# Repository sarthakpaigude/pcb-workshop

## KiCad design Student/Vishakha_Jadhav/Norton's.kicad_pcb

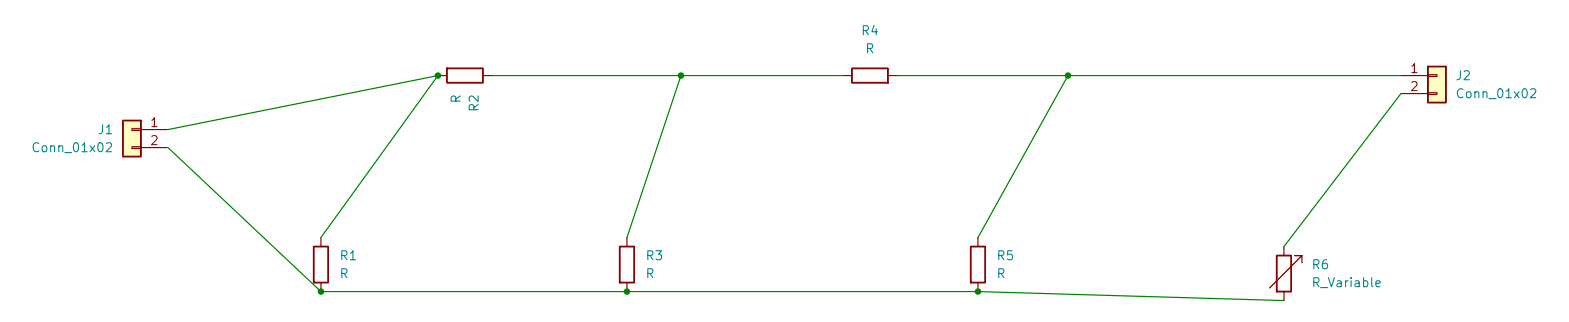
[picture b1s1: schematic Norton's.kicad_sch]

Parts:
J1, J2: Conn_01x02; PinHeader_1x02_P2.54mm_Vertical
R1, R2, R3, R4, R5: R; R_Axial_DIN0207_L6.3mm_D2.5mm_P15.24mm_Horizontal
R6: R_Variable; R_Box_L26.0mm_W5.0mm_P20.00mm

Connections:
unnamed: J1.1, R1.1, R2.2
unnamed: J1.2, R1.2, R3.2, R5.2, R6.2
unnamed: J2.1, R4.2, R5.1
unnamed: J2.2, R6.1
unnamed: R2.1, R3.1, R4.1

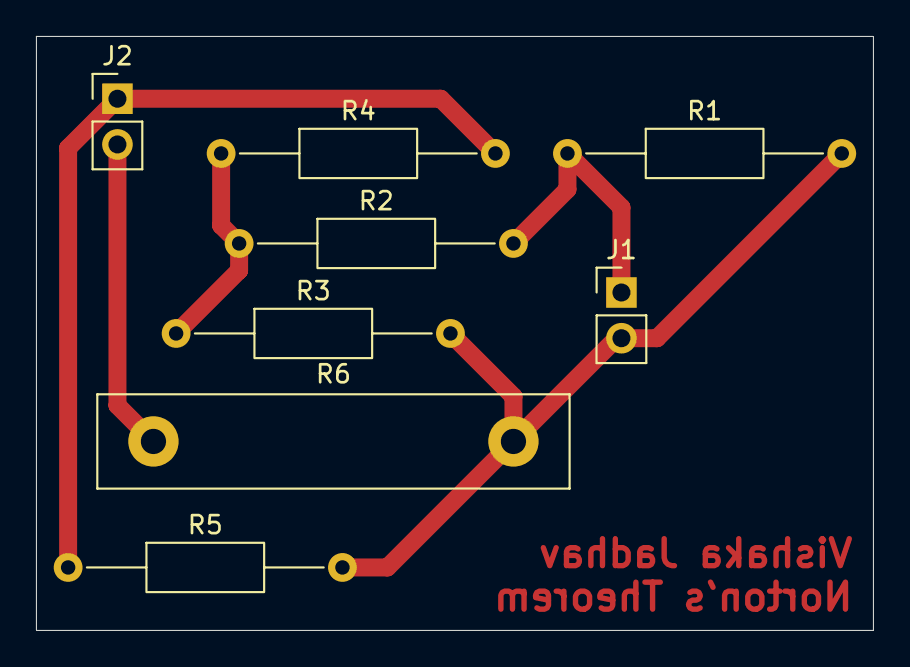
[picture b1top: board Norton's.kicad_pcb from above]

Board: 2 copper layers, 46.5 x 33.0 mm, 8 parts (0 on the bottom side), 5 nets.

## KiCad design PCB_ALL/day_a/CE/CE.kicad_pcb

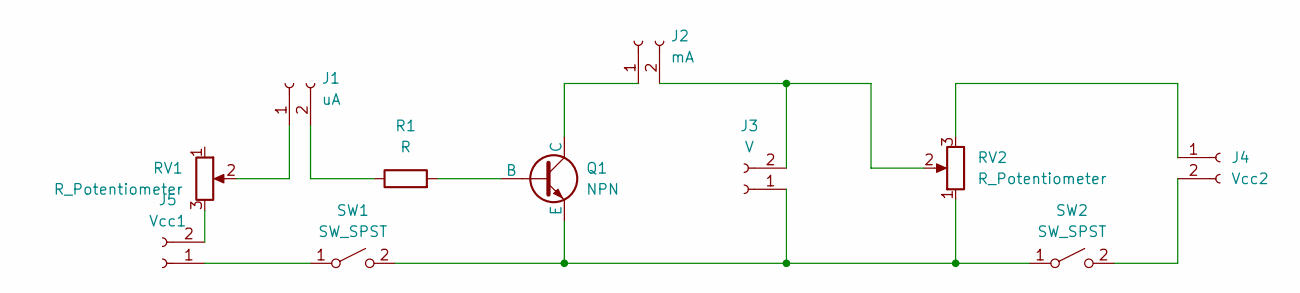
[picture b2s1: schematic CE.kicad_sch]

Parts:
J1: uA; Banana_Jack_2Pin
J2: mA; Banana_Jack_2Pin
J3: V; Banana_Jack_2Pin
J4: Vcc2; Banana_Jack_2Pin
J5: Vcc1; Banana_Jack_2Pin
Q1: NPN; TO-92L_Inline_Wide
R1: R; R_Axial_DIN0204_L3.6mm_D1.6mm_P7.62mm_Horizontal
RV1, RV2: R_Potentiometer; Potentiometer_Vishay_248GJ-249GJ_Single_Vertical
SW1, SW2: SW_SPST; SW_DIP_SPSTx01_Slide_6.7x4.1mm_W7.62mm_P2.54mm_LowProfile

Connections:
unnamed: J1.1, RV1.2
unnamed: J1.2, R1.1
unnamed: J2.1, Q1.1 (C)
unnamed: J2.2, J3.2, RV2.2
unnamed: J3.1, Q1.3 (E), RV2.1, SW1.2 (B), SW2.1 (A)
unnamed: J4.1, RV2.3
unnamed: J4.2, SW2.2 (B)
unnamed: J5.1, SW1.1 (A)
unnamed: J5.2, RV1.3
unnamed: Q1.2 (B), R1.2

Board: 2 copper layers, 11 parts (0 on the bottom side), 10 nets, no tracks yet.

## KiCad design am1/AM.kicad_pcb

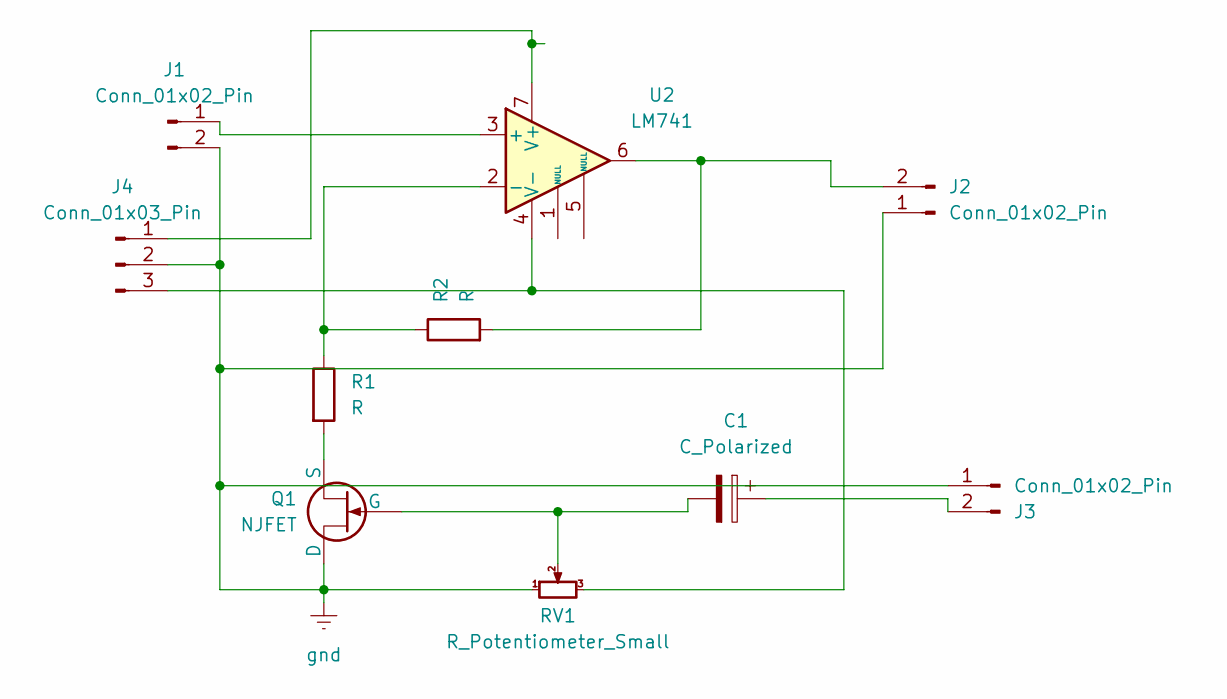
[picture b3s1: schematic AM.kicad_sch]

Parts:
C1: C_Polarized; CP_Radial_D8.0mm_P5.00mm
J1, J2, J3: Conn_01x02_Pin; Banana_Jack_2Pin
J4: Conn_01x03_Pin; Banana_Jack_3Pin
Q1: NJFET; TO-72-4
R1, R2: R; R_Axial_DIN0309_L9.0mm_D3.2mm_P12.70mm_Horizontal
RV1: R_Potentiometer_Small; Potentiometer_Alps_RK163_Single_Horizontal
U2: LM741; DIP-8_W7.62mm

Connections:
unnamed: J1.1, U2.3 (+)
unnamed: J2.2, R2.2, U2.6
unnamed: C1.1, J3.2
unnamed: J4.1, U2.7 (V+)
unnamed: J4.3, RV1.3, U2.4 (V-)
unnamed: C1.2, Q1.2 (G), RV1.2
unnamed: Q1.3 (S), R1.2
unnamed: R1.1, R2.1, U2.2 (-)
gnd: J1.2, J2.1, J3.1, J4.2, Q1.1 (D), RV1.1

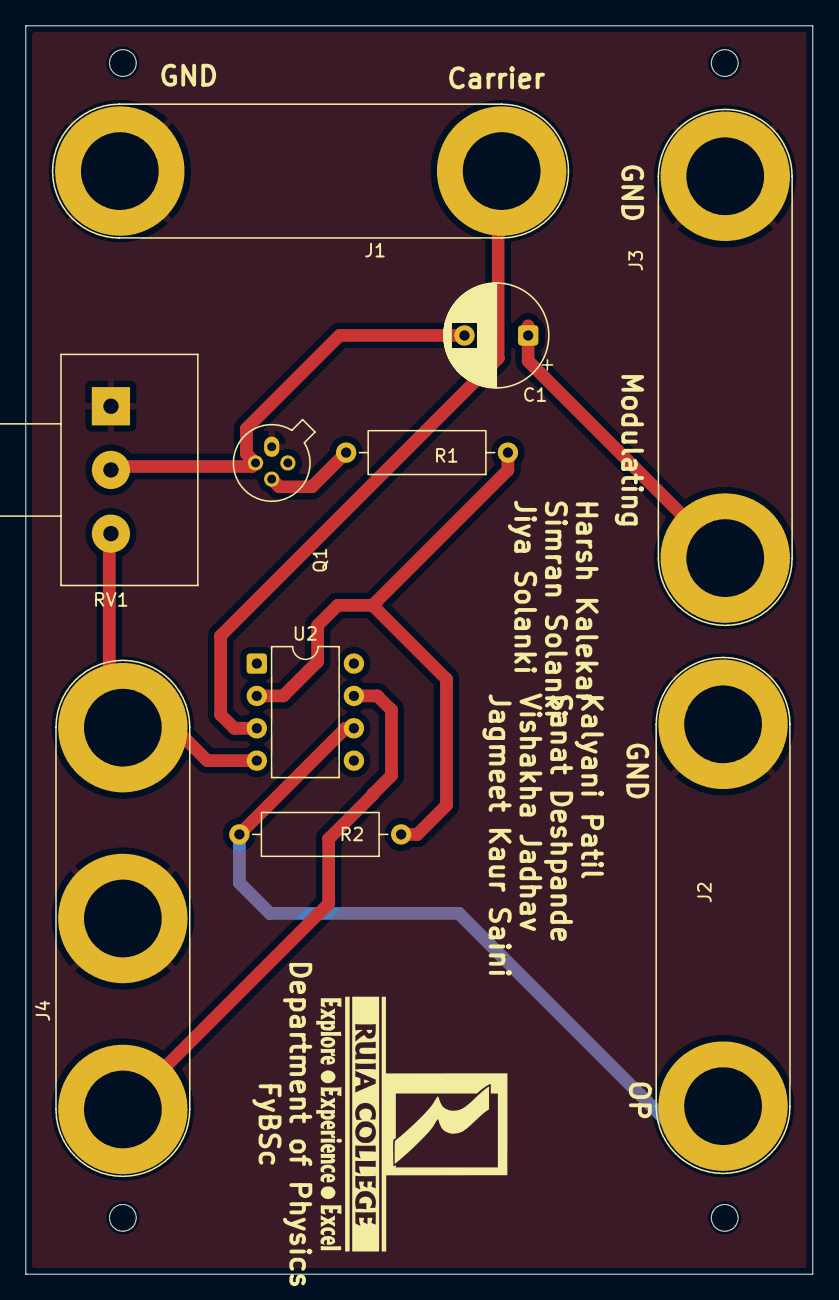
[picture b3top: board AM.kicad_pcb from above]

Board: 2 copper layers, 61.8 x 98.0 mm, 10 parts (0 on the bottom side), 9 nets.

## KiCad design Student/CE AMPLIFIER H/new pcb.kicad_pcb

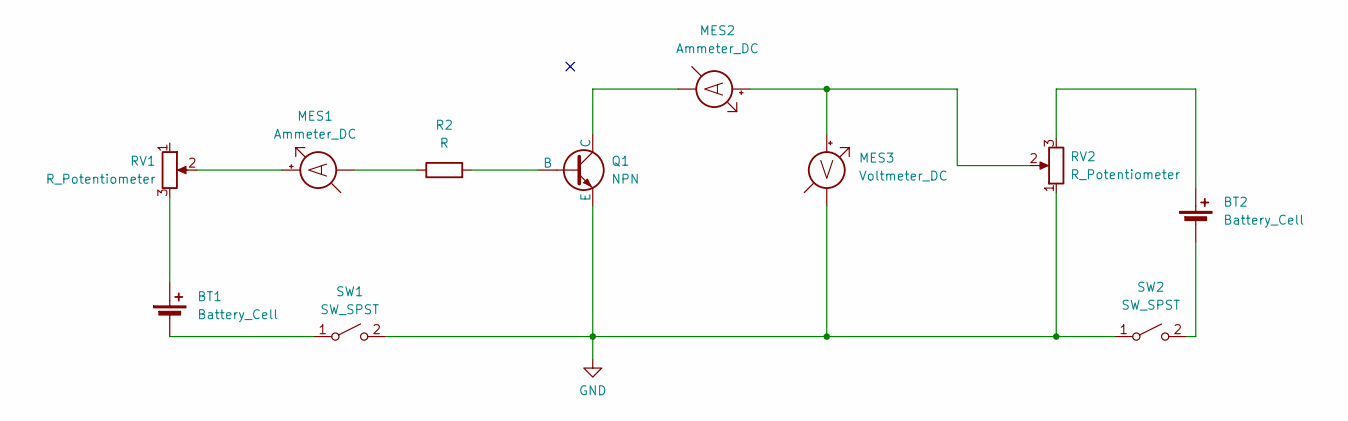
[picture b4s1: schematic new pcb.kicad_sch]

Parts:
BT1, BT2: Battery_Cell; Banana_Jack_2Pin
MES1, MES2: Ammeter_DC; Banana_Jack_2Pin
MES3: Voltmeter_DC; Banana_Jack_2Pin
Q1: NPN; TO-92
R2: R; R_Axial_DIN0207_L6.3mm_D2.5mm_P7.62mm_Horizontal
RV1, RV2: R_Potentiometer; Potentiometer_Vishay_148-149_Single_Vertical
SW1, SW2: SW_SPST; SW_DIP_SPSTx01_Slide_6.7x4.1mm_W7.62mm_P2.54mm_LowProfile

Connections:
GND: MES3.1 (-), Q1.3 (E), RV2.1, SW1.2 (B), SW2.1 (A)
unnamed: BT1.1 (+), RV1.3
unnamed: BT1.2 (-), SW1.1 (A)
unnamed: BT2.1 (+), RV2.3
unnamed: BT2.2 (-), SW2.2 (B)
unnamed: MES1.2 (+), RV1.2
unnamed: MES1.1 (-), R2.1
unnamed: MES2.2 (+), MES3.2 (+), RV2.2
unnamed: MES2.1 (-), Q1.1 (C)
unnamed: Q1.2 (B), R2.2

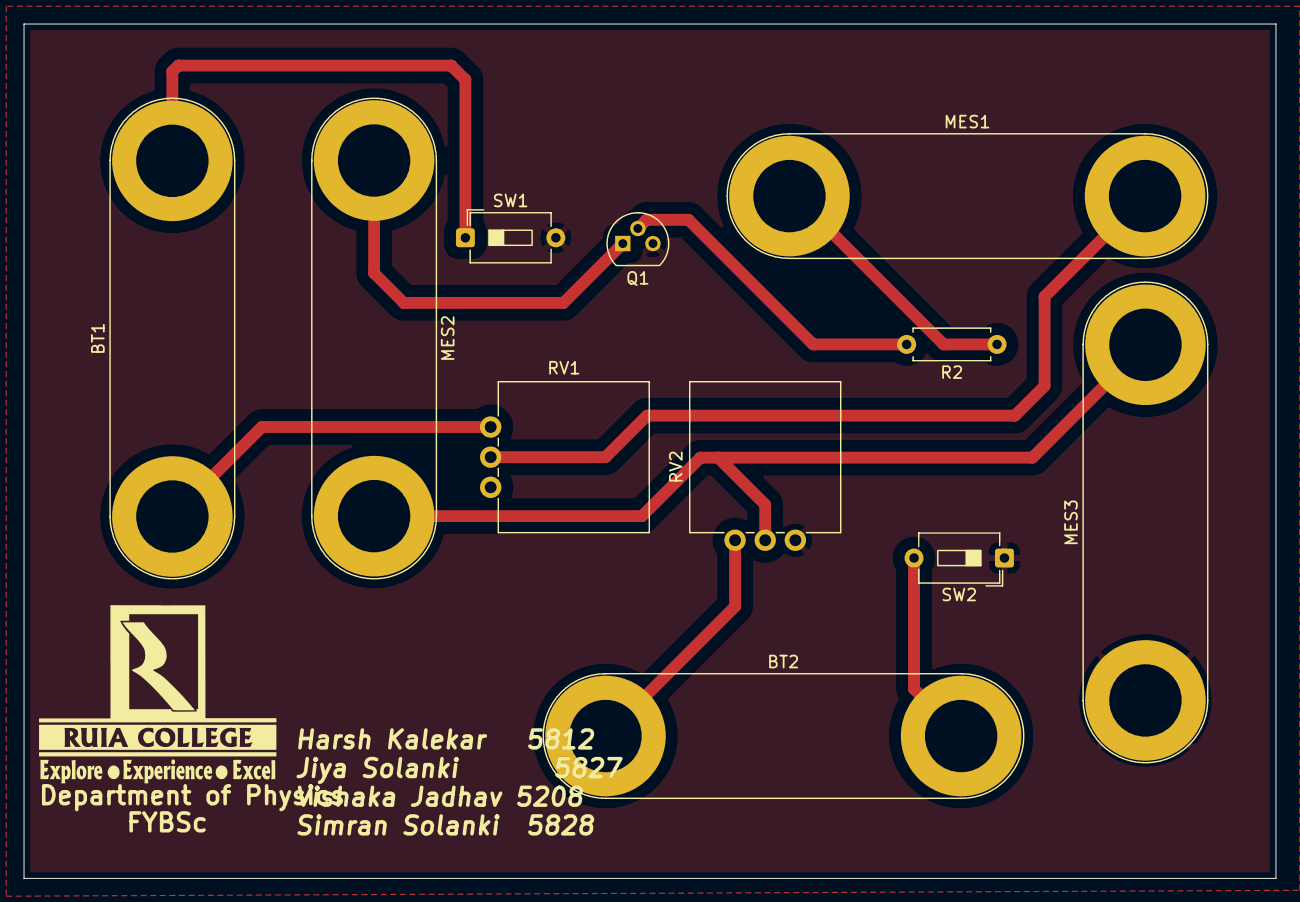
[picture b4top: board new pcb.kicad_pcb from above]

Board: 2 copper layers, 105.5 x 72.0 mm, 11 parts (0 on the bottom side), 10 nets.

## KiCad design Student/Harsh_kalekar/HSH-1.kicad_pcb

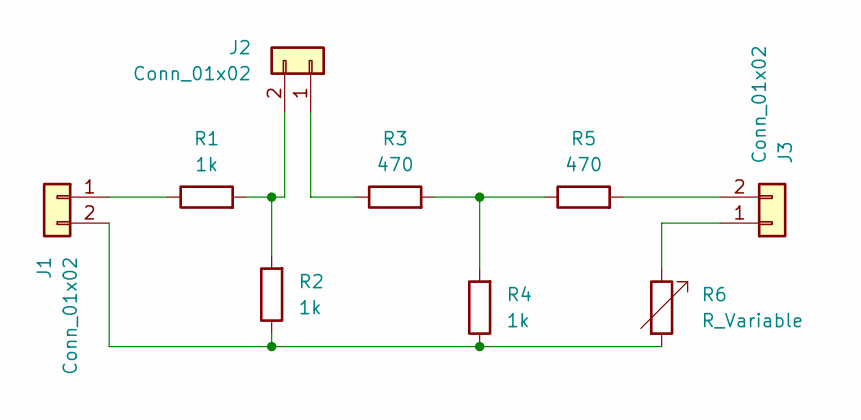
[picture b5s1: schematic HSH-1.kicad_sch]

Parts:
J1, J2, J3: Conn_01x02; PinHeader_1x02_P2.54mm_Vertical
R1, R2, R4: 1k; R_Axial_DIN0207_L6.3mm_D2.5mm_P7.62mm_Horizontal
R3, R5: 470; R_Axial_DIN0207_L6.3mm_D2.5mm_P7.62mm_Horizontal
R6: R_Variable; R_Box_L14.0mm_W5.0mm_P9.00mm

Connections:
unnamed: J1.1, R1.1
unnamed: J1.2, R2.1, R4.1, R6.2
unnamed: J2.1, R3.1
unnamed: J2.2, R1.2, R2.2
unnamed: J3.1, R6.1
unnamed: J3.2, R5.2
unnamed: R3.2, R4.2, R5.1

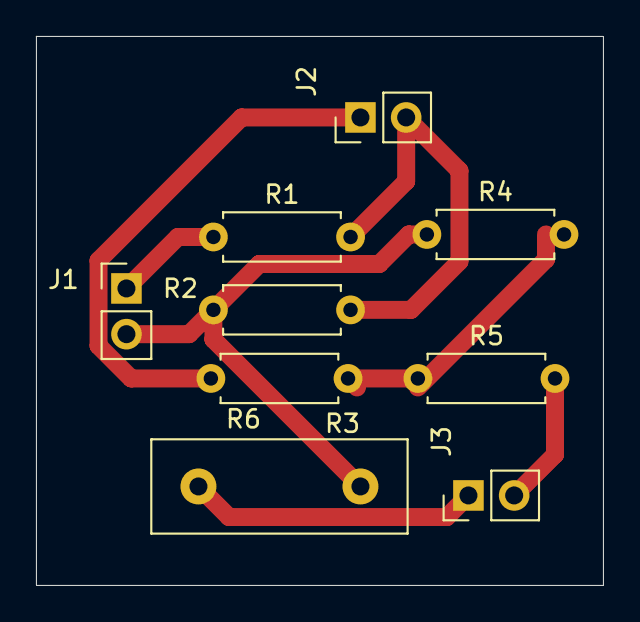
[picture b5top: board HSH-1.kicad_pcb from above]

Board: 2 copper layers, 31.5 x 30.5 mm, 9 parts (0 on the bottom side), 7 nets.

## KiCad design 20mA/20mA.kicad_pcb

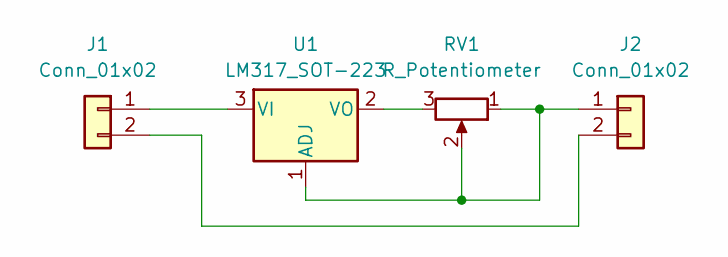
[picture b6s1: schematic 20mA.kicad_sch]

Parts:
J1, J2: Conn_01x02; Banana_Jack_2Pin
RV1: R_Potentiometer; Potentiometer_Runtron_RM-063_Horizontal
U1: LM317_SOT-223; SOT-223-3_TabPin2

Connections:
unnamed: J1.1, U1.3 (VI)
unnamed: J1.2, J2.2
unnamed: J2.1, RV1.1, RV1.2, U1.1 (ADJ)
unnamed: RV1.3, U1.2 (VO)

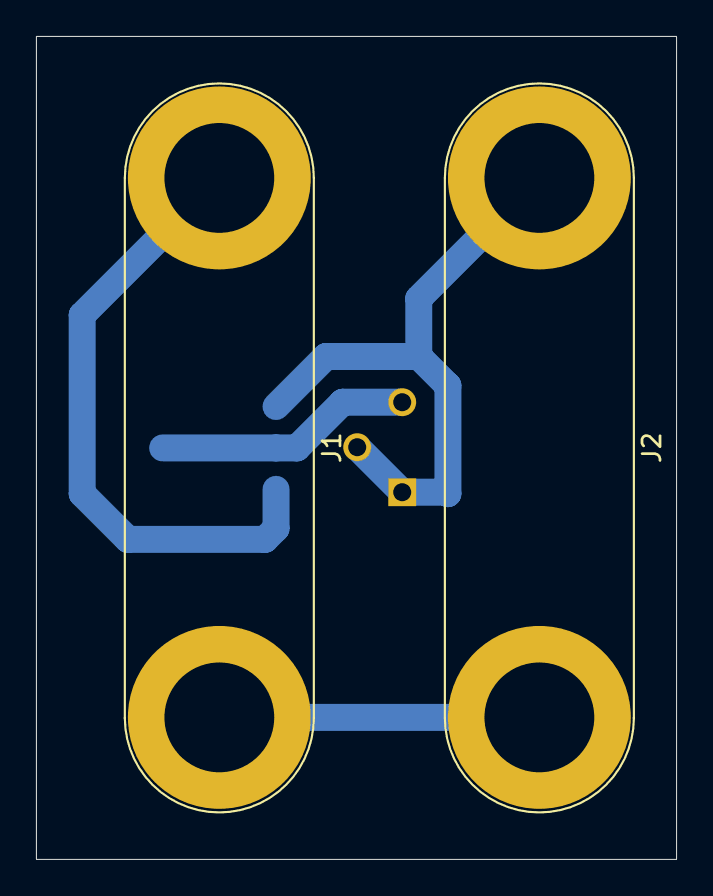
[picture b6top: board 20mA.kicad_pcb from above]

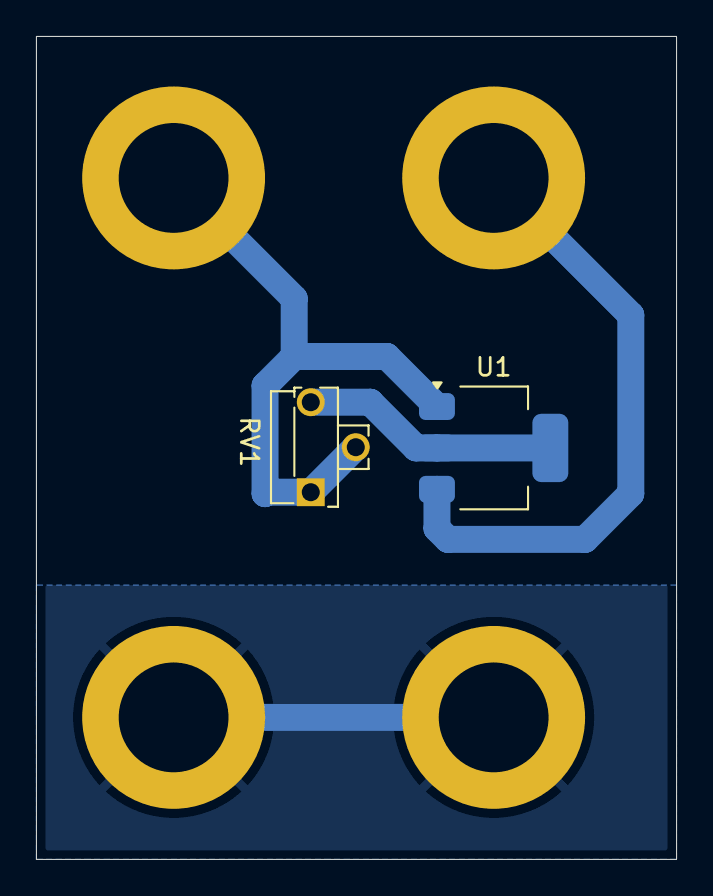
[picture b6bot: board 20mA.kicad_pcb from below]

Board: 2 copper layers, 35.6 x 45.7 mm, 4 parts (2 on the bottom side), 4 nets.

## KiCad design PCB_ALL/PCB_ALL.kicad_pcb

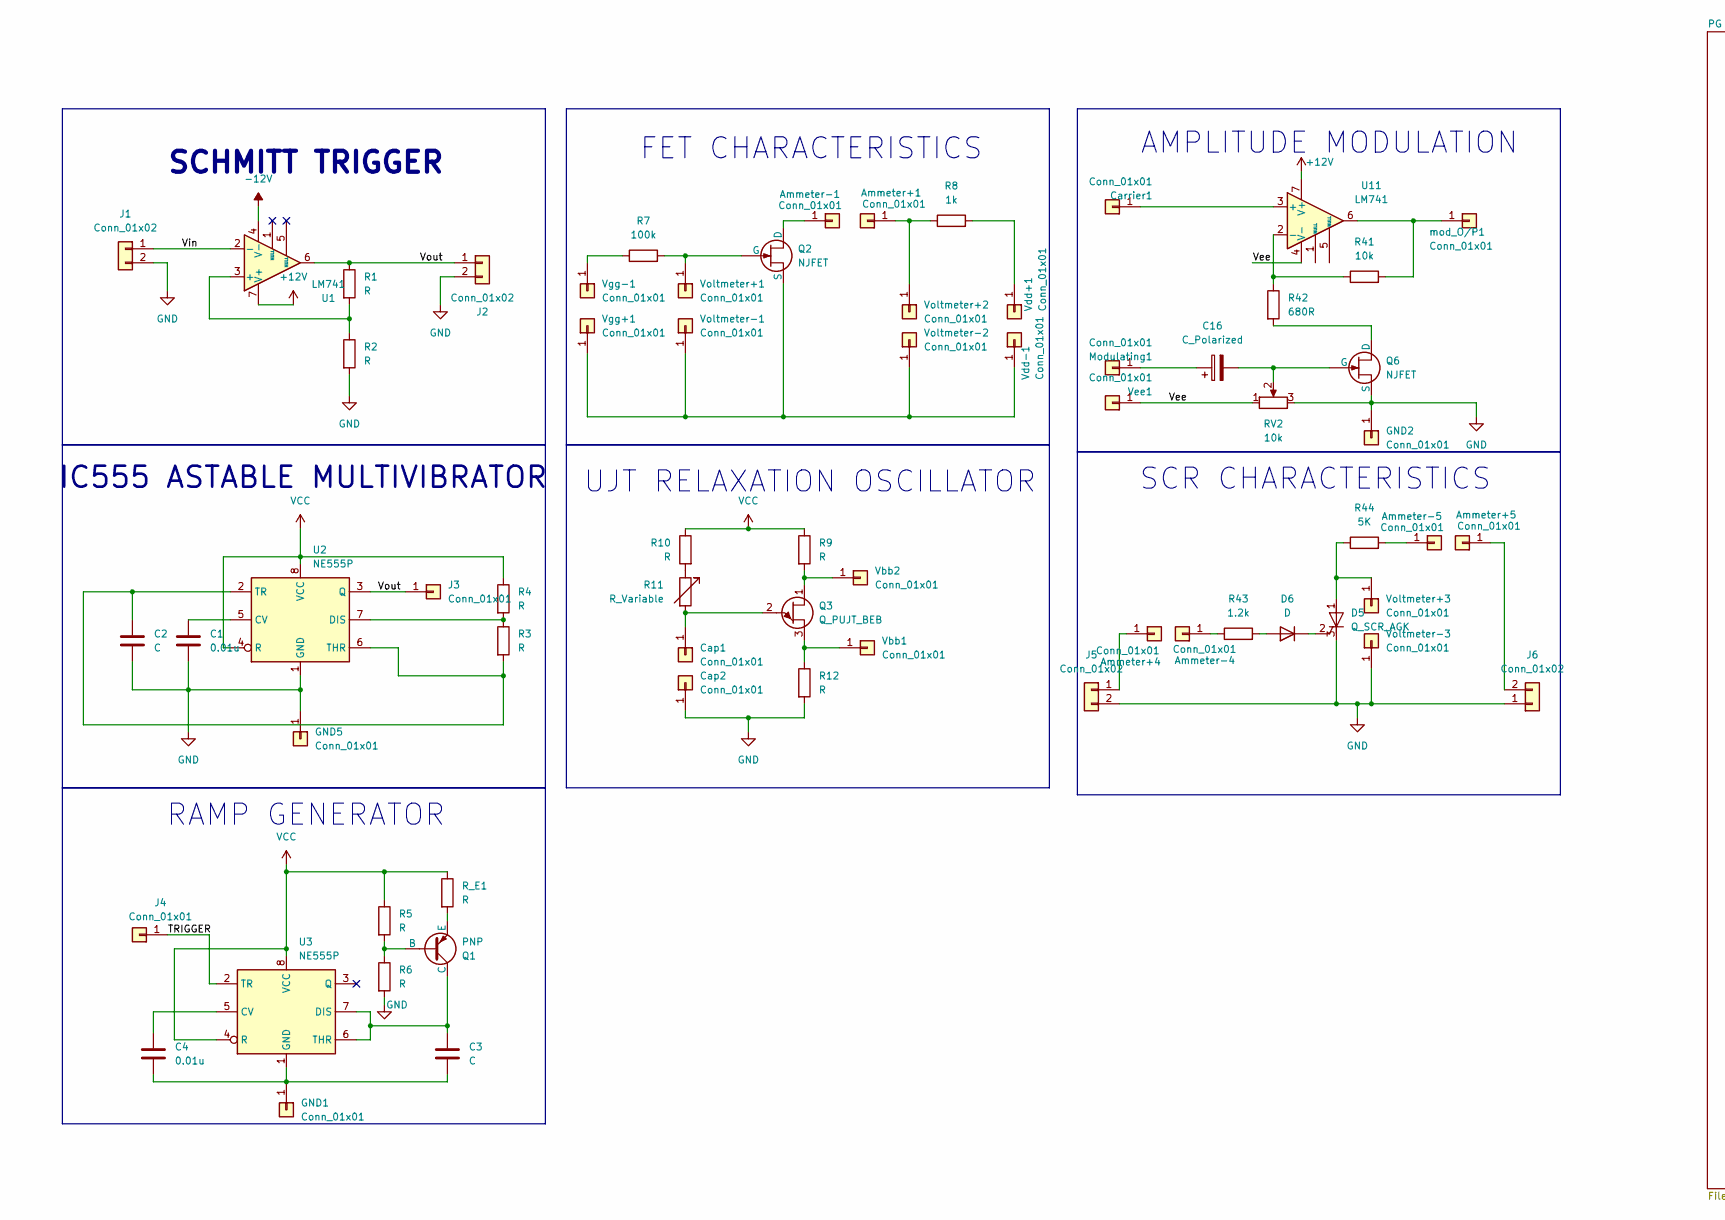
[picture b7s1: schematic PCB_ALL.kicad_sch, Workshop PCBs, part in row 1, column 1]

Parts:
Ammeter+1, Ammeter+4, Ammeter+5: Conn_01x01; PinSocket_1x01_P2.54mm_Vertical
Ammeter-1, Ammeter-4, Ammeter-5: Conn_01x01; PinSocket_1x01_P2.54mm_Vertical
C1, C4: 0.01u; C_0805_2012Metric_Pad1.18x1.45mm_HandSolder
C2, C3: C; C_0805_2012Metric_Pad1.18x1.45mm_HandSolder
C16: C_Polarized; CP_Radial_D5.0mm_P2.50mm
Cap1, Cap2: Conn_01x01; PinSocket_1x01_P2.54mm_Vertical
Carrier1: Conn_01x01; PinSocket_1x01_P2.54mm_Vertical
D5: Q_SCR_AGK; TO-92
D6: D; D_0805_2012Metric
GND1, GND2, GND5: Conn_01x01; PinSocket_1x01_P2.54mm_Vertical
J1, J2, J5, J6: Conn_01x02; PinSocket_1x02_P2.54mm_Vertical
J3, J4: Conn_01x01; PinSocket_1x01_P2.54mm_Vertical
Modulating1: Conn_01x01; PinSocket_1x01_P2.54mm_Vertical
Q1: PNP; TO-92_HandSolder
Q2: NJFET; TO-92_HandSolder
Q3: Q_PUJT_BEB; TO-92_HandSolder
Q6: NJFET; SOT-23
R1, R2, R3, R4, R5, R6, R9, R10, R12: R; R_0805_2012Metric_Pad1.20x1.40mm_HandSolder
R7: 100k; R_0805_2012Metric_Pad1.20x1.40mm_HandSolder
R8: 1k; R_0805_2012Metric_Pad1.20x1.40mm_HandSolder
R11: R_Variable; R_Axial_DIN0207_L6.3mm_D2.5mm_P7.62mm_Horizontal
R41: 10k; R_0805_2012Metric_Pad1.20x1.40mm_HandSolder
R42: 680R; R_0805_2012Metric_Pad1.20x1.40mm_HandSolder
R43: 1.2k; R_0805_2012Metric_Pad1.20x1.40mm_HandSolder
R44: 5K; R_0805_2012Metric_Pad1.20x1.40mm_HandSolder
RV2: 10k; Potentiometer_Bourns_3296P_Horizontal
R_E1: R; R_Axial_DIN0207_L6.3mm_D2.5mm_P7.62mm_Horizontal
U1, U11: LM741; SOIC-8_3.9x4.9mm_P1.27mm
U2, U3: NE555P; SOIC-8_3.9x4.9mm_P1.27mm
Vbb1, Vbb2: Conn_01x01; PinSocket_1x01_P2.54mm_Vertical
Vdd+1: Conn_01x01; PinSocket_1x01_P2.54mm_Vertical
Vdd-1: Conn_01x01; PinSocket_1x01_P2.54mm_Vertical
Vee1: Conn_01x01; PinSocket_1x01_P2.54mm_Vertical
Vgg+1: Conn_01x01; PinSocket_1x01_P2.54mm_Vertical
Vgg-1: Conn_01x01; PinSocket_1x01_P2.54mm_Vertical
Voltmeter+1, Voltmeter+2, Voltmeter+3: Conn_01x01; PinSocket_1x01_P2.54mm_Vertical
Voltmeter-1, Voltmeter-2, Voltmeter-3: Conn_01x01; PinSocket_1x01_P2.54mm_Vertical
mod_O/P1: Conn_01x01; PinSocket_1x01_P2.54mm_Vertical

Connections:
+12V: U1.7 (V+), U11.7 (V+); also elsewhere on the board
-12V: U1.4 (V-); also elsewhere on the board
/TRIGGER: J4.1, U3.2 (TR)
/Vee: RV2.1, U11.4 (V-), Vee1.1
/Vin: J1.1, U1.2 (-)
/Vout: J2.1, J3.1, R1.1, U1.6, U2.3 (Q)
GND: C1.2, C2.2, Cap2.1, D5.3 (K), GND2.1, GND5.1, J1.2, J2.2, J5.2, J6.1, Q6.3 (S), R2.2, R6.2, R12.2, RV2.3, U2.1 (GND), Voltmeter-3.1; also elsewhere on the board
unnamed: Ammeter+1.1, R8.1, Voltmeter+2.1
unnamed 12: Ammeter+4.1, J5.1; also elsewhere on the board
unnamed 13: Ammeter+5.1, J6.2; also elsewhere on the board
unnamed: Ammeter-1.1, Q2.1 (D)
unnamed 17: Ammeter-4.1, R43.1; also elsewhere on the board
unnamed 18: Ammeter-5.1, R44.2; also elsewhere on the board
unnamed: Cap1.1, Q3.2 (E), R11.2
unnamed: Carrier1.1, U11.3 (+)
unnamed 38: D5.1 (A), R44.1, Voltmeter+3.1; also elsewhere on the board
unnamed: D5.2 (G), D6.1 (K)
unnamed: D6.2 (A), R43.2
unnamed: C3.2, C4.2, GND1.1, U3.1 (GND)
unnamed: C16.1, Modulating1.1
unnamed: Q1.2 (B), R5.2, R6.1
unnamed: C3.1, Q1.1 (C), U3.6 (THR), U3.7 (DIS)
unnamed: Q1.3 (E), R_E1.2
unnamed: Q2.2 (G), R7.2, Voltmeter+1.1
unnamed: Q2.3 (S), Vdd-1.1, Vgg+1.1, Voltmeter-1.1, Voltmeter-2.1
unnamed: Q3.3 (B1), R12.1, Vbb1.1
unnamed: Q3.1 (B2), R9.2, Vbb2.1
unnamed: Q6.1 (D), R42.2
unnamed: C16.2, Q6.2 (G), RV2.2
unnamed: R10.2, R11.1
unnamed: R1.2, R2.1, U1.3 (+)
unnamed: C1.1, U2.5 (CV)
unnamed: R3.1, R4.2, U2.7 (DIS)
unnamed: C2.1, R3.2, U2.2 (TR), U2.6 (THR)
unnamed: C4.1, U3.5 (CV)
unnamed: R41.1, R42.1, U11.2 (-)
unnamed: R8.2, Vdd+1.1
unnamed: R7.1, Vgg-1.1
unnamed: R41.2, U11.6, mod_O/P1.1
VCC: R4.1, R5.1, R9.1, R10.1, R_E1.1, U2.4 (R), U2.8 (VCC), U3.4 (R), U3.8 (VCC); also elsewhere on the board

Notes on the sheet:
UJT RELAXATION OSCILLATOR
SCR CHARACTERISTICS
SCHMITT TRIGGER
IC555 ASTABLE MULTIVIBRATOR
RAMP GENERATOR
AMPLITUDE MODULATION
FET CHARACTERISTICS

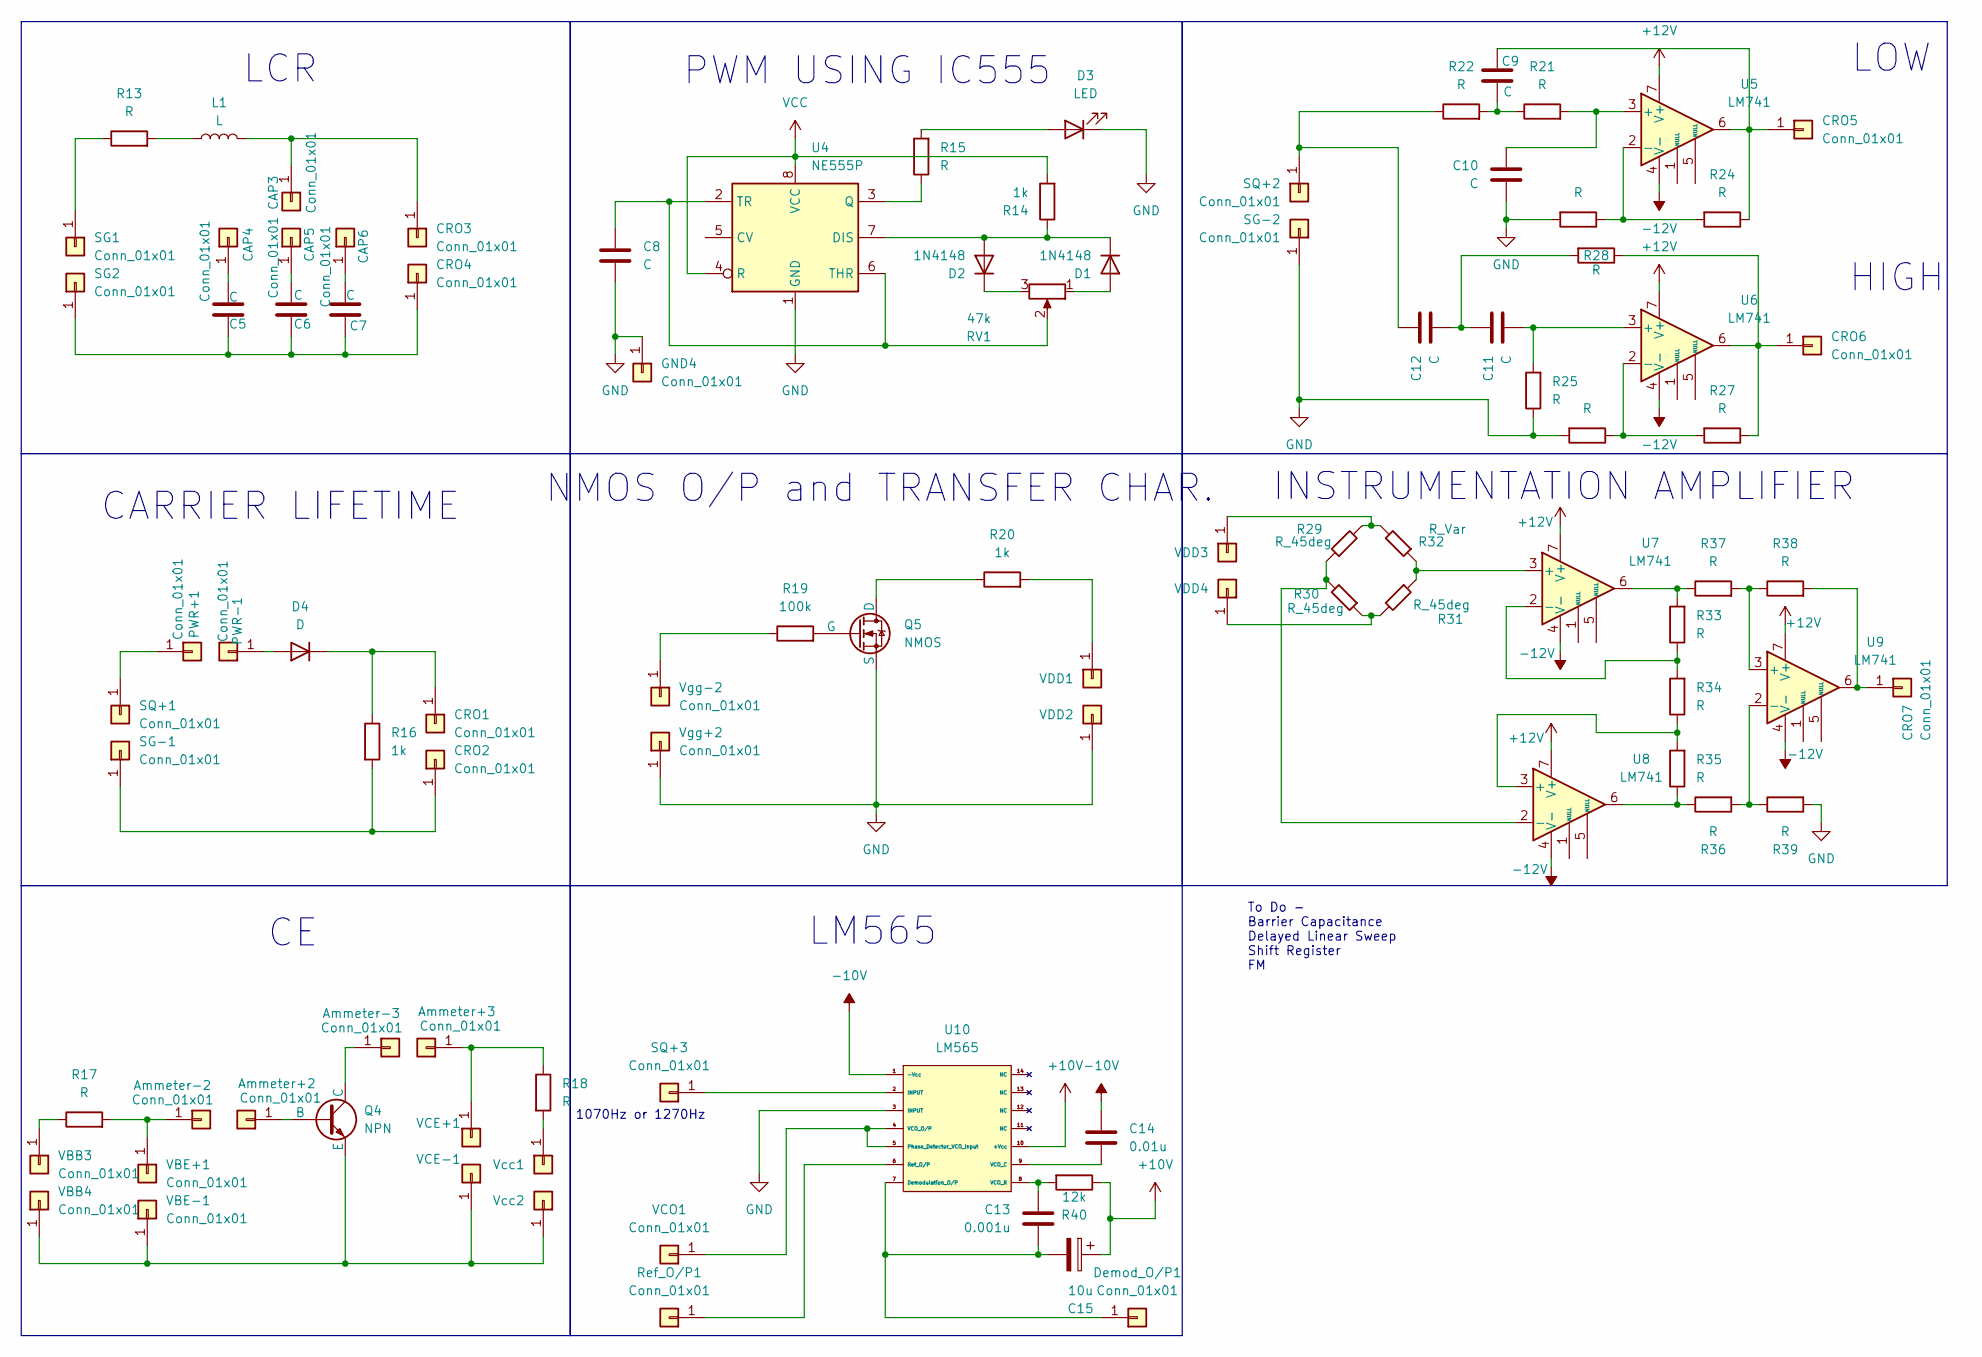
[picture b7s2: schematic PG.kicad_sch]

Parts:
Ammeter+2, Ammeter+3: Conn_01x01; PinSocket_1x01_P2.54mm_Vertical
Ammeter-2, Ammeter-3: Conn_01x01; PinSocket_1x01_P2.54mm_Vertical
C5, C6, C7, C8, C9, C10, C11, C12: C; C_0805_2012Metric_Pad1.18x1.45mm_HandSolder
C13: 0.001u; C_0805_2012Metric_Pad1.18x1.45mm_HandSolder
C14: 0.01u; C_0805_2012Metric_Pad1.18x1.45mm_HandSolder
C15: 10u; CP_Radial_D5.0mm_P2.50mm
CAP3, CAP4, CAP5, CAP6: Conn_01x01; PinSocket_1x01_P2.54mm_Vertical
CRO1, CRO2, CRO3, CRO4, CRO5, CRO6, CRO7: Conn_01x01; PinSocket_1x01_P2.54mm_Vertical
D1, D2: 1N4148; D_DO-35_SOD27_P7.62mm_Horizontal
D3: LED; LED_D3.0mm
D4: D; D_A-405_P7.62mm_Horizontal
Demod_O/P1: Conn_01x01; PinSocket_1x01_P2.54mm_Vertical
GND4: Conn_01x01; PinSocket_1x01_P2.54mm_Vertical
L1: L; L_Axial_L5.3mm_D2.2mm_P7.62mm_Horizontal_Vishay_IM-1
PWR+1: Conn_01x01; PinSocket_1x01_P2.54mm_Vertical
PWR-1: Conn_01x01; PinSocket_1x01_P2.54mm_Vertical
Q4: NPN; SOT-23
Q5: NMOS; SOT-23
R13, R15, R17, R18, R21, R22, R23, R24, R25, R26, R27, R28, R33, R34, R35, R36, R37, R38, R39: R; R_0805_2012Metric_Pad1.20x1.40mm_HandSolder
R14, R16, R20: 1k; R_0805_2012Metric_Pad1.20x1.40mm_HandSolder
R19: 100k; R_0805_2012Metric_Pad1.20x1.40mm_HandSolder
R29, R30, R31: R_45deg; R_0805_2012Metric_Pad1.20x1.40mm_HandSolder
R32: R_Var; PinSocket_2x01_P2.54mm_Vertical
R40: 12k; R_0805_2012Metric_Pad1.20x1.40mm_HandSolder
RV1: 47k; Potentiometer_Bourns_3296P_Horizontal
Ref_O/P1: Conn_01x01; PinHeader_1x01_P2.54mm_Vertical
SG1, SG2: Conn_01x01; PinSocket_1x01_P2.54mm_Vertical
SG-1, SG-2: Conn_01x01; PinSocket_1x01_P2.54mm_Vertical
SQ+1, SQ+2, SQ+3: Conn_01x01; PinSocket_1x01_P2.54mm_Vertical
U4: NE555P; SOIC-8_3.9x4.9mm_P1.27mm
U5, U6, U7, U8, U9: LM741; SOIC-8_3.9x4.9mm_P1.27mm
U10: LM565; CERDIP-14_W7.62mm_SideBrazed_LongPads
VBB3, VBB4: Conn_01x01; PinSocket_1x01_P2.54mm_Vertical
VBE+1: Conn_01x01; PinSocket_1x01_P2.54mm_Vertical
VBE-1: Conn_01x01; PinSocket_1x01_P2.54mm_Vertical
VCE+1: Conn_01x01; PinSocket_1x01_P2.54mm_Vertical
VCE-1: Conn_01x01; PinSocket_1x01_P2.54mm_Vertical
VCO1: Conn_01x01; PinSocket_1x01_P2.54mm_Vertical
VDD1, VDD2, VDD3, VDD4: Conn_01x01; PinSocket_1x01_P2.54mm_Vertical
Vcc1, Vcc2: Conn_01x01; PinSocket_1x01_P2.54mm_Vertical
Vgg+2: Conn_01x01; PinSocket_1x01_P2.54mm_Vertical
Vgg-2: Conn_01x01; PinSocket_1x01_P2.54mm_Vertical

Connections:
+10V: C15.1, R40.1, U10.10 (+Vcc)
+12V: U5.7 (V+), U6.7 (V+), U7.7 (V+), U8.7 (V+), U9.7 (V+); also elsewhere on the board
-10V: C14.2, U10.1 (-Vcc)
-12V: U5.4 (V-), U6.4 (V-), U7.4 (V-), U8.4 (V-), U9.4 (V-); also elsewhere on the board
GND: C8.2, C10.2, D3.1 (K), GND4.1, Q5.3 (S), R23.2, R25.1, R26.2, R39.2, SG-2.1, U4.1 (GND), U10.3 (INPUT), VDD2.1, Vgg+2.1; also elsewhere on the board
unnamed 10: Ammeter+2.1, Q4.2 (B); also elsewhere on the board
unnamed 11: Ammeter+3.1, R18.1, VCE+1.1; also elsewhere on the board
unnamed 15: Ammeter-2.1, R17.2, VBE+1.1; also elsewhere on the board
unnamed 16: Ammeter-3.1, Q4.1 (C); also elsewhere on the board
unnamed: C9.2, R21.1, R22.2
unnamed: C11.1, C12.2, R28.2
unnamed: CAP3.1, CRO3.1, L1.2
unnamed: C5.1, CAP4.1
unnamed: C6.1, CAP5.1
unnamed: C7.1, CAP6.1
unnamed: CRO1.1, D4.1 (K), R16.1
unnamed: CRO2.1, R16.2, SG-1.1
unnamed: C5.2, C6.2, C7.2, CRO4.1, SG2.1
unnamed: C9.1, CRO5.1, R24.1, U5.6
unnamed: CRO6.1, R27.1, R28.1, U6.6
unnamed: CRO7.1, R38.2, U9.6
unnamed: D1.2 (A), RV1.1
unnamed: D1.1 (K), D2.2 (A), R14.1, U4.7 (DIS)
unnamed: D2.1 (K), RV1.3
unnamed: D3.2 (A), R15.2
unnamed: D4.2 (A), PWR-1.1
unnamed: C13.1, C15.2, Demod_O/P1.1, U10.7 (Demodulation_O/P)
unnamed: L1.1, R13.2
unnamed: PWR+1.1, SQ+1.1
unnamed: Q4.3 (E), VBB4.1, VBE-1.1, VCE-1.1, Vcc2.1
unnamed: Q5.1 (D), R20.1
unnamed: Q5.2 (G), R19.2
unnamed: R33.2, R37.1, U7.6
unnamed: R35.1, R36.1, U8.6
unnamed: Ref_O/P1.1, U10.6 (Ref_O/P)
unnamed: R13.1, SG1.1
unnamed: C12.1, R22.1, SQ+2.1
unnamed: SQ+3.1, U10.2 (INPUT)
unnamed: R15.1, U4.3 (Q)
unnamed: C8.1, RV1.2, U4.2 (TR), U4.6 (THR)
unnamed: C10.1, R21.2, U5.3 (+)
unnamed: R23.1, R24.2, U5.2 (-)
unnamed: C11.2, R25.2, U6.3 (+)
unnamed: R26.1, R27.2, U6.2 (-)
unnamed: R31.1, R32.1, U7.3 (+)
unnamed: R33.1, R34.2, U7.2 (-)
unnamed: R34.1, R35.2, U8.3 (+)
unnamed: R29.1, R30.2, U8.2 (-)
unnamed: R37.2, R38.1, U9.3 (+)
unnamed: R36.2, R39.1, U9.2 (-)
unnamed: U10.4 (VCO_O/P), U10.5 (Phase_Detector_VCO_Input), VCO1.1
unnamed: C14.1, U10.9 (VCO_C)
unnamed: C13.2, R40.2, U10.8 (VCO_R)
unnamed: R17.1, VBB3.1
unnamed: R20.2, VDD1.1
unnamed: R29.2, R32.2, VDD3.1
unnamed: R30.1, R31.2, VDD4.1
unnamed: R18.2, Vcc1.1
unnamed: R19.1, Vgg-2.1
VCC: R14.2, U4.4 (R), U4.8 (VCC); also elsewhere on the board

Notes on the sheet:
CARRIER LIFETIME
LM565
LOW
1070Hz or 1270Hz
PWM USING IC555
HIGH
NMOS O/P and TRANSFER CHAR.
INSTRUMENTATION AMPLIFIER
LCR
To Do - Barrier Capacitance Delayed Linear Sweep Shift Register FM

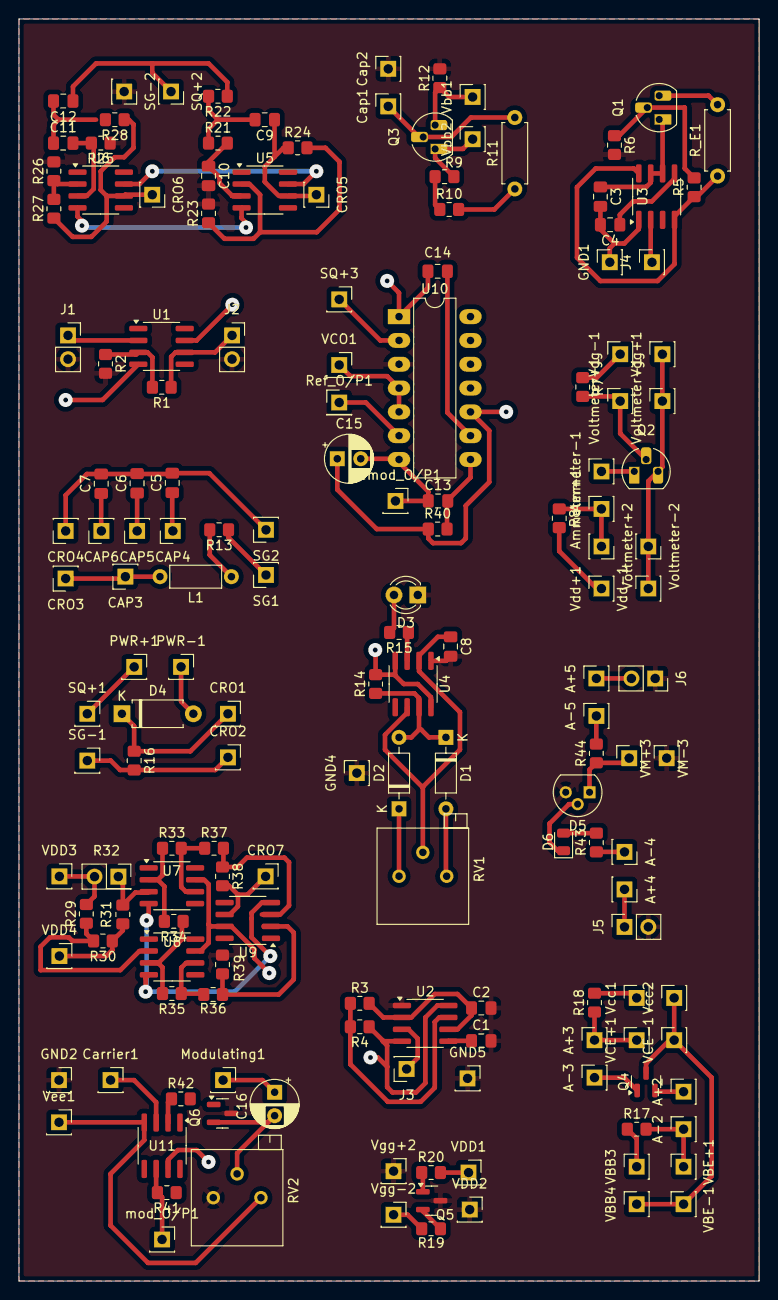
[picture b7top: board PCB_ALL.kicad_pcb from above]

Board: 2 copper layers, 78.9 x 134.6 mm, 162 parts (0 on the bottom side), 96 nets.

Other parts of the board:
A+2, A+3, A+4, A+5: Conn_01x01; PinSocket_1x01_P2.54mm_Vertical
A-2, A-3, A-4, A-5: Conn_01x01; PinSocket_1x01_P2.54mm_Vertical
VM+3: Conn_01x01; PinSocket_1x01_P2.54mm_Vertical
VM-3: Conn_01x01; PinSocket_1x01_P2.54mm_Vertical

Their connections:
GND: VM-3.1; also elsewhere on the board
unnamed 10: A+2.1; also elsewhere on the board
unnamed 11: A+3.1; also elsewhere on the board
unnamed 12: A+4.1; also elsewhere on the board
unnamed 13: A+5.1; also elsewhere on the board
unnamed 15: A-2.1; also elsewhere on the board
unnamed 16: A-3.1; also elsewhere on the board
unnamed 17: A-4.1; also elsewhere on the board
unnamed 18: A-5.1; also elsewhere on the board
unnamed 38: VM+3.1; also elsewhere on the board

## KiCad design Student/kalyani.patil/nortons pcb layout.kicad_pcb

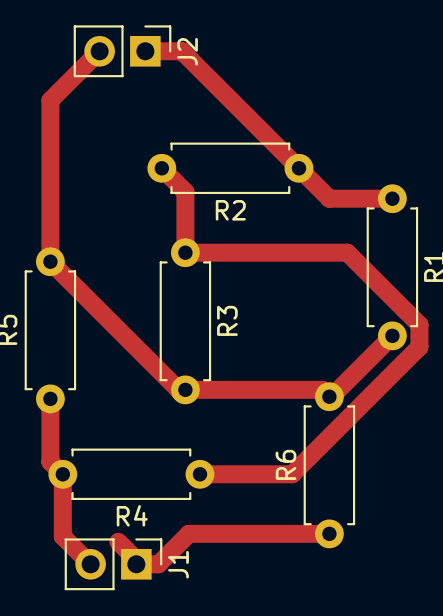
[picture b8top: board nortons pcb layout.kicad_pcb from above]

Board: 2 copper layers, 8 parts (0 on the bottom side), 5 nets.

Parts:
J1, J2: Conn_01x02; PinHeader_1x02_P2.54mm_Vertical
R1, R2, R3, R4, R5: R; R_Axial_DIN0207_L6.3mm_D2.5mm_P7.62mm_Horizontal
R6: R_Variable; R_Axial_DIN0207_L6.3mm_D2.5mm_P7.62mm_Horizontal

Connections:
unnamed: J1.1, R6.1
unnamed: J1.2, R4.2, R5.1
unnamed: J2.1, R1.1, R2.1
unnamed: J2.2, R1.2, R3.2, R5.2, R6.2
unnamed: R2.2, R3.1, R4.1

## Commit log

2025-09-11 Initial commit - uploaded project files
2025-09-11 Deleted some files
2025-09-12 Add .gitignore for KiCAD backups
2025-09-12 Updated KiCAD project files
2025-10-15 Updated KiCAD schematic and PCB layout
2026-03-09 Added project folders
